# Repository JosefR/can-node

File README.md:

# can-node

A simple STM32F072 evaluation board with temperature and humidity sensors and a CAN interface.

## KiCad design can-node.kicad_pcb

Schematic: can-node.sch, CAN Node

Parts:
P2: CONN_01X04; WAGO_218-104

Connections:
CANH_IN: P2.4; also elsewhere on the board
CANL_IN: P2.3; also elsewhere on the board
GND: P2.2; also elsewhere on the board
VIN+: P2.1; also elsewhere on the board

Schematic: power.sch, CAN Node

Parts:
C1: 2.2µF; C_2010_5025Metric_Pad1.52x2.65mm_HandSolder
C2: 100n >10V; C_0603_1608Metric_Pad1.05x0.95mm_HandSolder; Rating >10V
C3: 22µF; C_1206_3216Metric_Pad1.42x1.75mm_HandSolder
C22: 0.1F; C_Radial_D13_L7_P10
D1: 40.2V; D_SMA_Handsoldering; Part P4SMA47CA
D2: 1A, 50V; D_SMF_Handsoldering; MPN SS1FN6
D3: 0.57V 1A; D_SOD-123_HandSoldering
D6: 0.3V; D_SOD-123_HandSoldering
L1: 27µH 220mΩ; SDE0604A_HandSoldering
R2: 100k; R_0603_1608Metric_Pad1.05x0.95mm_HandSolder
R3: 28k 1%; R_0603_1608Metric_Pad1.05x0.95mm_HandSolder
R4: 8.45k 1%; R_0603_1608Metric_Pad1.05x0.95mm_HandSolder
R15: 100; R_0805_2012Metric_Pad1.33x1.40mm_HandSolder
U1: LMR16006; TI-DDC_HandSoldering
W8: VINB; Measurement_Point_tiny
W9: VINC; Measurement_Point_tiny
W10: FB; Measurement_Point_tiny
W11: SW; Measurement_Point_tiny
W12: +3.3V; Measurement_Point_tiny
W15: 3.3V; TH-Pad_1.5mm
W19: GND; TH-Pad_1.5mm

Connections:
+BATT: D6.1 (K), R15.1; also elsewhere on the board
/Power Supply/VIN: C1.1, D2.1 (K), R2.1, U1.5, W8.1, W9.1
GND: C1.2, C3.2, C22.2, D1.2, D3.2 (A), R4.2, U1.2, W19.1; also elsewhere on the board
unnamed: C2.1, D3.1 (K), L1.1, U1.6, W11.1
unnamed: C2.2, U1.1
unnamed: C22.1, R15.2
unnamed: R2.2, U1.4
unnamed: R3.2, R4.1, U1.3, W10.1
VIN+: D1.1, D2.2 (A); also elsewhere on the board

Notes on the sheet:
9..24 V
3.3V 0.6A

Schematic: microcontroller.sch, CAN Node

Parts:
C4, C5: 15p; C_0603_1608Metric_Pad1.05x0.95mm_HandSolder
C6, C10, C16: 4µ7; C_0805_2012Metric_Pad1.33x1.40mm_HandSolder
C7, C8, C9, C11, C12, C13, C14, C15, C17, C18, C19: 100n; C_0603_1608Metric_Pad1.05x0.95mm_HandSolder
C20: 4n7; C_0603_1608Metric_Pad1.05x0.95mm_HandSolder
D4, D5: red; LED_0603_HandSoldering
P1: Debug; micromatch_smd_2x05
R5, R6: 10k; R_0603_1608Metric_Pad1.05x0.95mm_HandSolder
R7, R8: 220; R_0603_1608Metric_Pad1.05x0.95mm_HandSolder
R9, R12: 3.3k; R_0603_1608Metric_Pad1.05x0.95mm_HandSolder
R10, R11: 3k3; R_0603_1608Metric_Pad1.05x0.95mm_HandSolder
R13, R14: 60.4 1%; R_0603_1608Metric_Pad1.05x0.95mm_HandSolder
SW1, SW2, SW3: SW_PUSH; KMR2
U2: SN74LVC1G08; TI-DCK
U3: STM32F072RB; QFP-64_10x10_Pitch0.5mm_HandSoldering
U4: HDC1080; HDC1080_HandSoldering
U5: TCAN334; TI-DCN
W1: CAN_TX; Measurement_Point_tiny
W2: CAN_RX; Measurement_Point_tiny
W3: ~RST; Measurement_Point_tiny
W4: UART_RX; Measurement_Point_tiny
W5: UART_TX; Measurement_Point_tiny
W6: BOOT0; Measurement_Point_tiny
W16: SDA; Measurement_Point_tiny
W17: SCL; Measurement_Point_tiny
X1: 32.768KHz 12.5pF; Crystal-MS1V-T1K

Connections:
+BATT: U3.1; also elsewhere on the board
/Microcontroller/PA1: U3.15, U5.5
/Microcontroller/PA2: U3.16, U5.8
/Microcontroller/SWCLK: P1.4, U3.49
/Microcontroller/SWDIO: P1.3, U3.46
/Microcontroller/UART1_RX: P1.7, U3.43, W4.1; also elsewhere on the board
/Microcontroller/UART1_TX: P1.8, U3.42, W5.1; also elsewhere on the board
CANH_IN: R13.1, U5.7; also elsewhere on the board
CANL_IN: R14.2, U5.6; also elsewhere on the board
GND: C4.2, C5.2, C6.2, C7.2, C8.2, C9.2, C10.2, C11.2, C12.2, C13.2, C14.2, C15.2, C16.2, C17.2, C18.2, C19.2, C20.2, P1.9, P1.10, R7.1, R8.1, SW1.2, SW2.1, SW3.1, U2.3, U3.12, U3.18, U3.31, U3.47, U3.63, U4.2, U5.2; also elsewhere on the board
unnamed: C4.1, U3.3, X1.2
unnamed: C5.1, U3.4, X1.1
unnamed: C9.1, U2.4, U3.7, W3.1
unnamed: C15.1, R9.2, U3.33
unnamed: C17.1, R12.2, U3.34
unnamed: C20.1, R13.2, R14.1
unnamed: D4.1, R7.2
unnamed: D4.2, U3.35
unnamed: D5.1, R8.2
unnamed: D5.2, U3.36
unnamed: P1.5, R6.2, U2.2
unnamed: R5.2, SW1.1, U2.1
unnamed: R9.1, SW2.2
unnamed: R10.2, U3.30, U4.1, W16.1
unnamed: R11.2, U3.29, U4.6, W17.1
unnamed: R12.1, SW3.2
unnamed: U3.60, W6.1
unnamed: U3.61, U5.4, W2.1
unnamed: U3.62, U5.1, W1.1
PC0: U3.8; also elsewhere on the board
PC1: U3.9; also elsewhere on the board
PC2: U3.10; also elsewhere on the board
PC3: U3.11; also elsewhere on the board
PC4: U3.24; also elsewhere on the board
PC5: U3.25; also elsewhere on the board
PC6: U3.37; also elsewhere on the board
PC7: U3.38; also elsewhere on the board
PC8: U3.39; also elsewhere on the board
PC9: U3.40; also elsewhere on the board
PC10: U3.51; also elsewhere on the board
PC11: U3.52; also elsewhere on the board
PC12: U3.53; also elsewhere on the board

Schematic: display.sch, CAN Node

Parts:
AFF1: LTC-4627
Q3, Q4, Q5, Q6, Q7, Q8, Q9, Q10: BSS138; SOT-23_Handsoldering
Q11, Q12, Q13, Q14, Q15: BSS84P; SOT-23_Handsoldering
R25, R26, R27, R28, R33, R34, R35, R36: 120; R_0603_1608Metric_Pad1.05x0.95mm_HandSolder

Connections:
GND: Q3.2 (S), Q4.2 (S), Q5.2 (S), Q6.2 (S), Q7.2 (S), Q8.2 (S), Q9.2 (S), Q10.2 (S); also elsewhere on the board
unnamed: AFF1.1, Q11.3
unnamed: AFF1.2, Q12.3
unnamed: AFF1.3, R28.1
unnamed: AFF1.4, Q15.3
unnamed: AFF1.5, R33.1
unnamed: AFF1.6, Q13.3
unnamed: AFF1.7, R36.1
unnamed: AFF1.8, Q14.3
unnamed: AFF1.11, R34.1
unnamed: AFF1.13, R27.1
unnamed: AFF1.14, R25.1
unnamed: AFF1.15, R35.1
unnamed: AFF1.16, R26.1
unnamed: Q3.3 (D), R25.2
unnamed: Q4.3 (D), R26.2
unnamed: Q5.3 (D), R27.2
unnamed: Q6.3 (D), R28.2
unnamed: Q7.3 (D), R33.2
unnamed: Q8.3 (D), R34.2
unnamed: Q9.3 (D), R35.2
unnamed: Q10.3 (D), R36.2
PC0: Q3.1 (G); also elsewhere on the board
PC1: Q4.1 (G); also elsewhere on the board
PC2: Q5.1 (G); also elsewhere on the board
PC3: Q6.1 (G); also elsewhere on the board
PC4: Q7.1 (G); also elsewhere on the board
PC5: Q8.1 (G); also elsewhere on the board
PC6: Q9.1 (G); also elsewhere on the board
PC7: Q10.1 (G); also elsewhere on the board
PC8: Q11.1; also elsewhere on the board
PC9: Q12.1; also elsewhere on the board
PC10: Q13.1; also elsewhere on the board
PC11: Q14.1; also elsewhere on the board
PC12: Q15.1; also elsewhere on the board

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
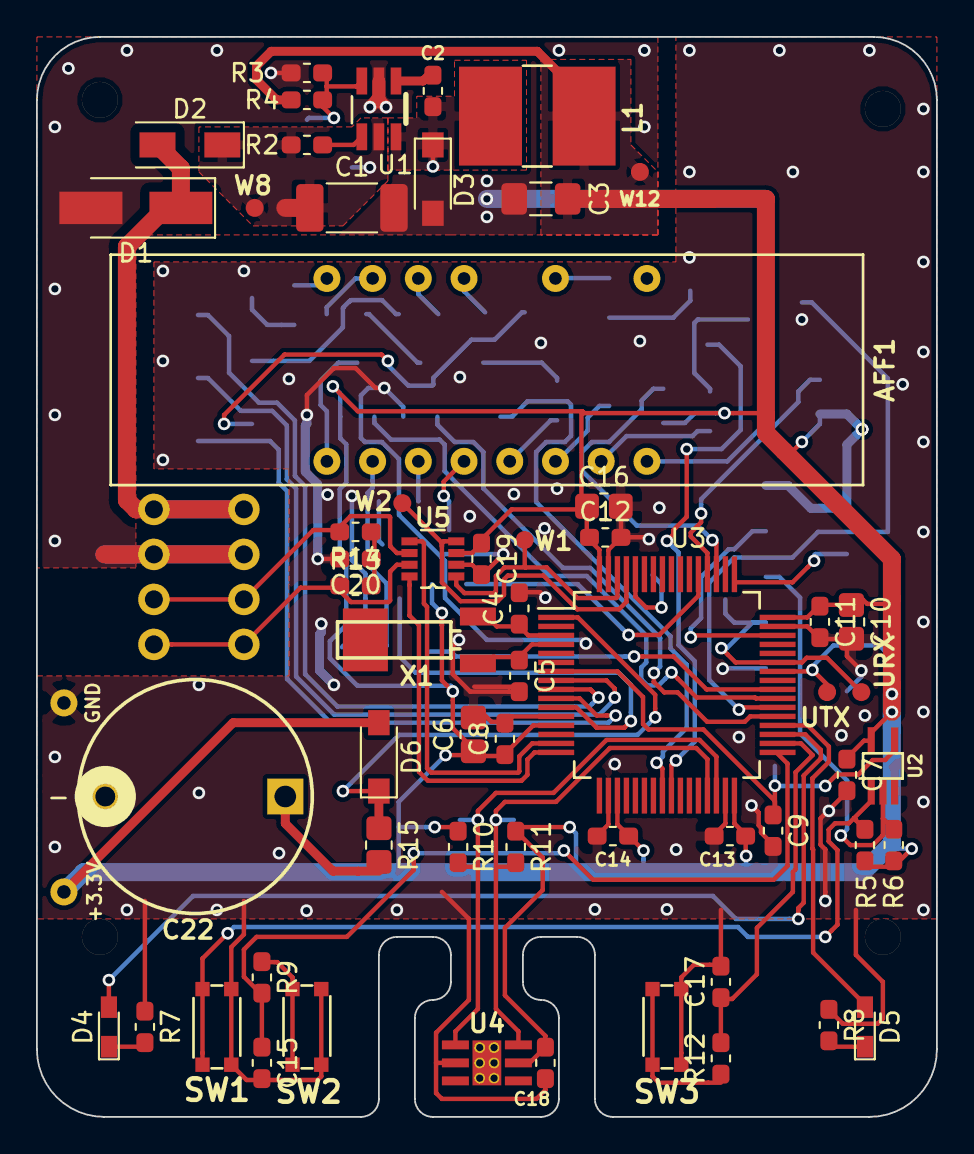
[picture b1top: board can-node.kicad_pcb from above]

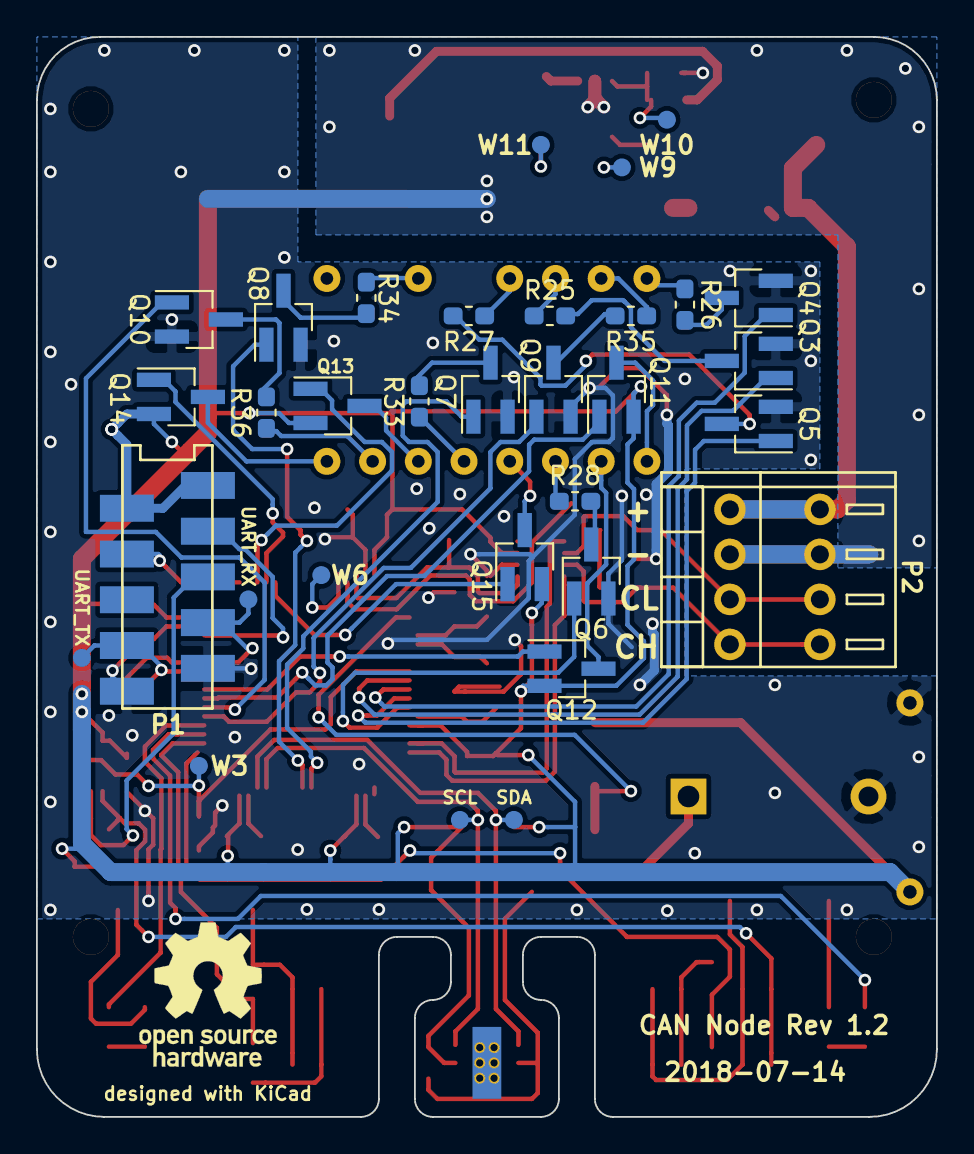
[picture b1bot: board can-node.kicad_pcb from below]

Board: 2 copper layers, 50.0 x 60.0 mm, 92 parts (32 on the bottom side), 71 nets.

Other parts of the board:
URX: UART_RX; Measurement_Point_tiny
UTX: UART_TX; Measurement_Point_tiny

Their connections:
/Microcontroller/UART1_RX: URX.1; also elsewhere on the board
/Microcontroller/UART1_TX: UTX.1; also elsewhere on the board

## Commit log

2015-10-28 A CAN node based on a STM32F072.
2015-11-02 Use LT8609 for power supply.
2015-11-02 Reverse voltage protection.
2015-11-07 changes on power supply; start redesign 3.3V rail
2016-08-13 Basic schematic with temparature and humidity sensor.
2016-08-13 Add flash and debug connector.
2016-08-20 HDC1080 footprint
2016-08-20 Use TPS5401 converter
2016-08-26 Use TI TCAN334 3.3V CAN transceiver.
2016-08-26 Remove 5V supply
2016-08-27 Reset circuit, minor changes
2016-09-02 24 V input protection
2016-09-02 Zener diode data sheet
2016-09-03 Add bom, minor changes
2016-09-10 Bom work
2016-09-10 Use LMR16006 DCDC
2016-09-17 Power supply work
2016-09-17 Remove power good logic
2016-10-28 Finish BOM, assign and add packages, set connectors, minor changes
2016-10-28 Add .gitignore
2016-10-29 Start PCB layout
2016-10-29 Use WAGO 218-106 connector
2016-10-29 Use solder jumper for optional CAN termination, fix crystal symbol
2016-10-31 Layouting ...
2016-11-03 Layout: first version
2016-11-03 Add case CAD file
2016-11-03 Fix drill holes for thermal vias of HDC1080
2016-11-03 Gerber and drill files
2016-11-19 ready?
2016-11-19 Use micro match for debug connector.
2016-11-19 Create a readme file.
2016-11-19 Remove datesheets from repository.
2016-12-03 Add measurement points, copyright label, minor changes.
2016-12-03 Minor changes (silkscreen)
2016-12-03 Update image, generate gerber again.
2016-12-03 Add schematic pdf.
2016-12-28 Add ambient light sensor, minor layout optimizations.
2016-12-28 Add missing schematic changes.
2016-12-29 Case modelling work
2017-01-05 Some modifications to schematic, BOM, start releayout
    - add LED display
    - change crystal for RTC
    - use components that are available at some distributors
2017-01-05 Layouting work
2017-01-07 Remove spi connector.
2017-01-10 Add 24V outputs.
2017-01-11 Remove unnecessary 24V out, minor changes.
2017-01-11 Minor changes.
2017-01-12 No real changes
2017-01-13 Add buffer capacitor for RTC.
2017-01-21 Create LICENSE
2017-02-20 Add schematic pdf and updated BOM.
2018-04-30 Update for KiCad 5. Assign hand solder foot prints.
2018-05-01 Make the board more hand solder friendly.
2018-05-02 Add mounting holes.
2018-05-02 Create pdf of schematic.
2018-07-13 Update for KiCad 5.
2018-07-14 Simplify over voltage protection and improve PCB.
    - use new KiCad library for some parts
2018-07-14 Replace remaining parts from old KiCad library.
2018-09-01 Update Gerber files.
